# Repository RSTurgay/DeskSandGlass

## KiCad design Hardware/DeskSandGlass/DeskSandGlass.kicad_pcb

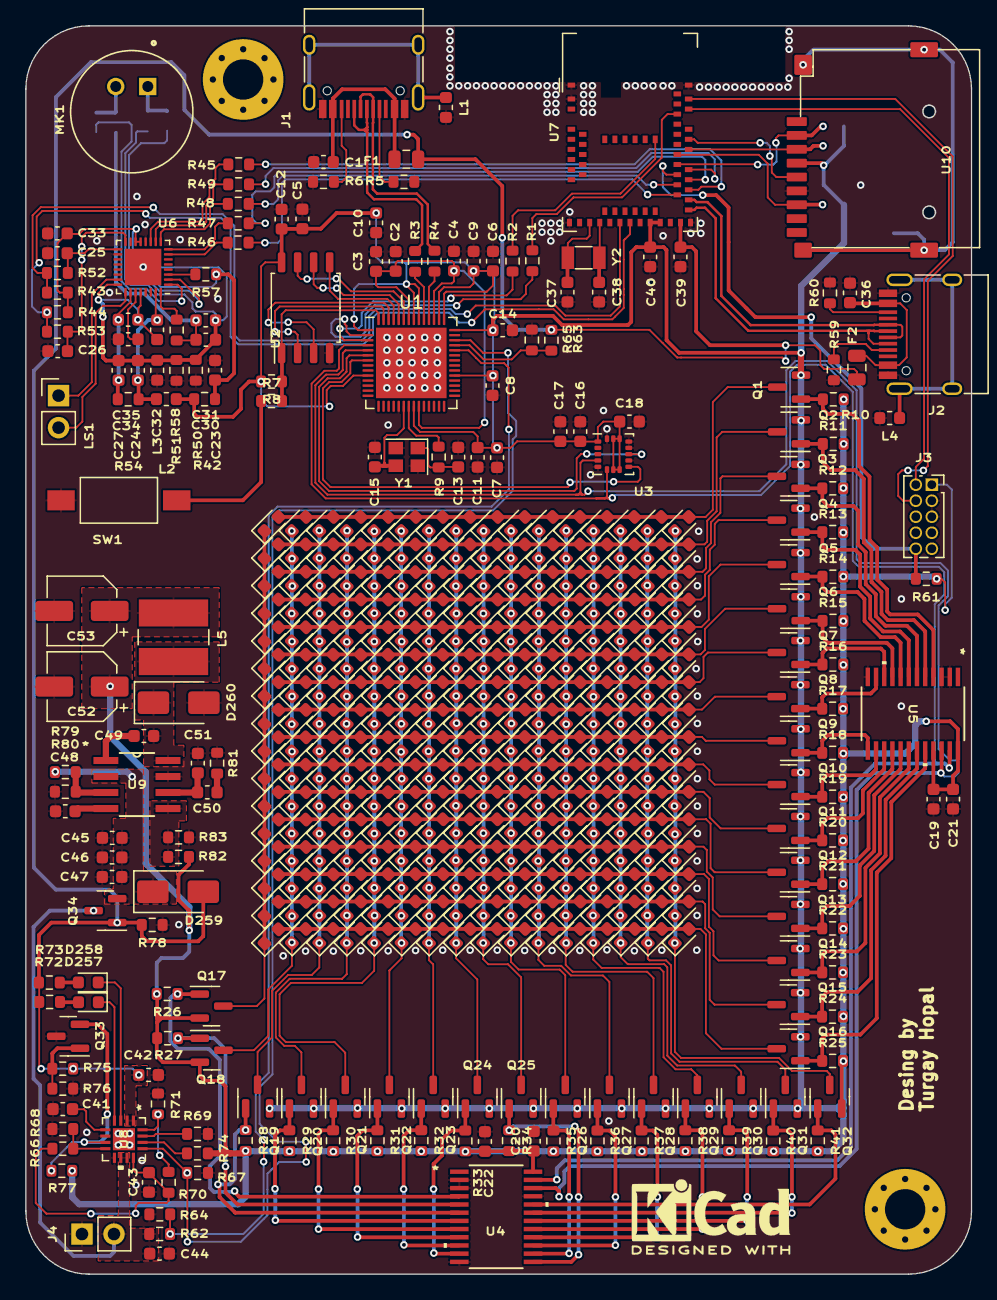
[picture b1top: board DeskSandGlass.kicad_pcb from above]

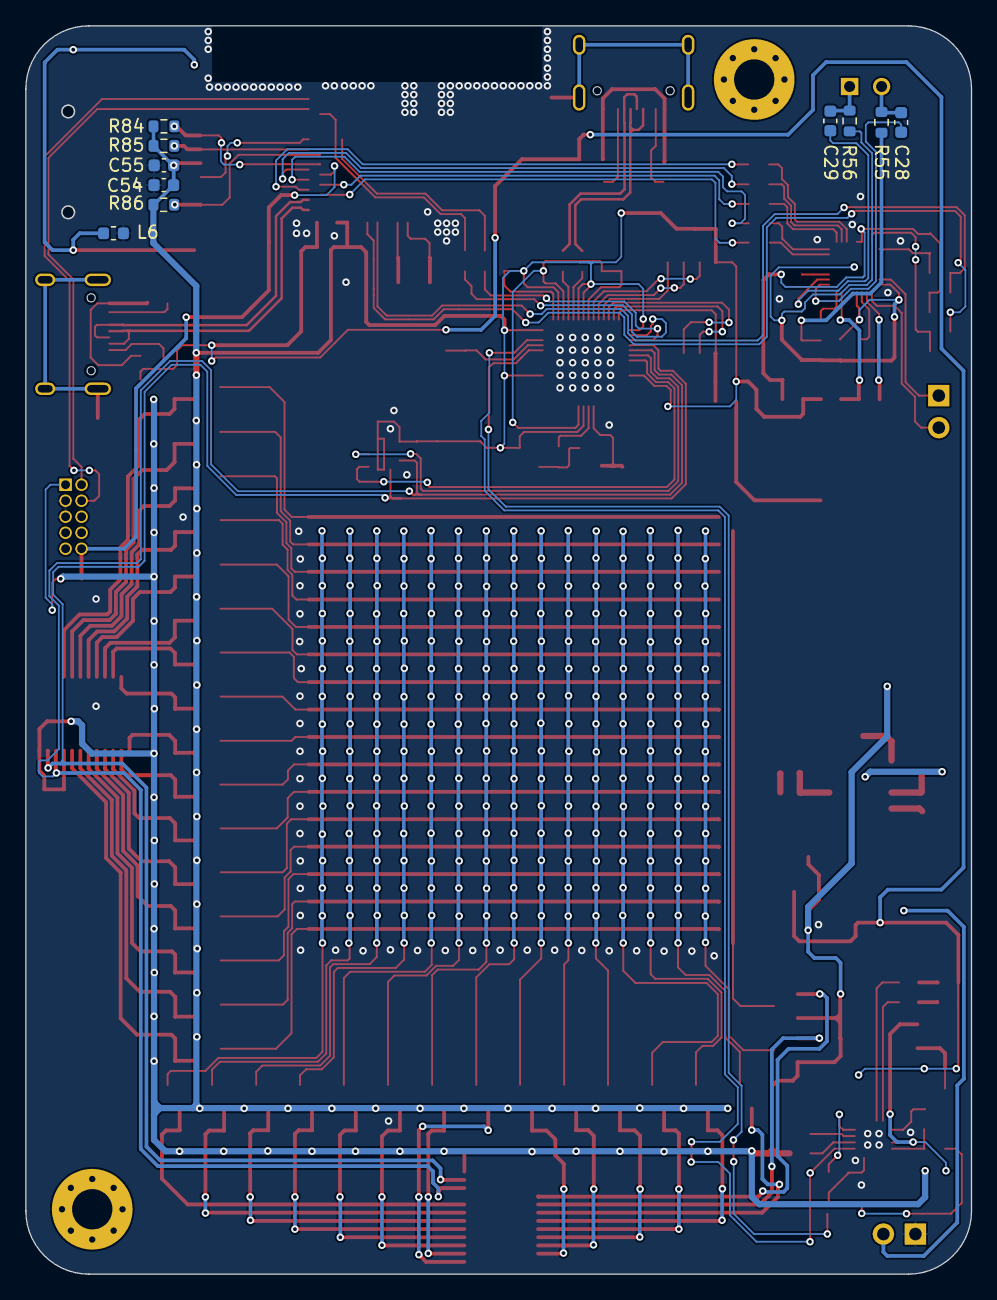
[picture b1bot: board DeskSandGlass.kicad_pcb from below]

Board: 2 copper layers, 75.0 x 99.0 mm, 462 parts (10 on the bottom side), 162 nets.

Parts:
C1, C4, C6, C21, C22, C28, C29, C36, C42: 1uF; C_0603_1608Metric
C2, C3, C5, C7, C8, C9, C10, C11, C12, C14, C16, C17, C19, C20, C31, C32, C33, C35, C54: 100nF; C_0603_1608Metric
C13, C15: 22pF; C_0603_1608Metric
C18, C23, C24, C25, C26, C27, C55: 10uF; C_0603_1608Metric
C30, C34, C39, C40, C44, C45, C46: 4.7uF; C_0603_1608Metric
C37, C38: 12pF; C_0603_1608Metric
C41, C47, C48: 10nF; C_0603_1608Metric
C43, C49, C50: 1nF; C_0603_1608Metric
C51: 47pF; C_0603_1608Metric
C52, C53: 47uF; CP_Elec_5x4.4
D1, D2, D3, D4, D5, D6, D7, D8, D9, D10, D11, D12, D13, D14, D15, D16, D17, D18, D19, D20, D21, D22, D23, D24, D25, D26, D27, D28, D29, D30, D31, D32, D33, D34, D35, D36, D37, D38, D39, D40, D41, D42, D43, D44, D45, D46, D47, D48, D49, D50, D51, D52, D53, D54, D55, D56, D57, D58, D59, D60, D61, D62, D63, D64, D65, D66, D67, D68, D69, D70, D71, D72, D73, D74, D75, D76, D77, D78, D79, D80, D81, D82, D83, D84, D85, D86, D87, D88, D89, D90, D91, D92, D93, D94, D95, D96, D97, D98, D99, D100, D101, D102, D103, D104, D105, D106, D107, D108, D109, D110, D111, D112, D113, D114, D115, D116, D117, D118, D119, D120, D121, D122, D123, D124, D125, D126, D127, D128, D129, D130, D131, D132, D133, D134, D135, D136, D137, D138, D139, D140, D141, D142, D143, D144, D145, D146, D147, D148, D149, D150, D151, D152, D153, D154, D155, D156, D157, D158, D159, D160, D161, D162, D163, D164, D165, D166, D167, D168, D169, D170, D171, D172, D173, D174, D175, D176, D177, D178, D179, D180, D181, D182, D183, D184, D185, D186, D187, D188, D189, D190, D191, D192, D193, D194, D195, D196, D197, D198, D199, D200, D201, D202, D203, D204, D205, D206, D207, D208, D209, D210, D211, D212, D213, D214, D215, D216, D217, D218, D219, D220, D221, D222, D223, D224, D225, D226, D227, D228, D229, D230, D231, D232, D233, D234, D235, D236, D237, D238, D239, D240, D241, D242, D243, D244, D245, D246, D247, D248, D249, D250, D251, D252, D253, D254, D255, D256, D257, D258: LED; LED_0603_1608Metric
D259: D; D_SMA
D260: B340; D_SMA
F1, F2: 6V/1.5A; Fuse_0805_2012Metric
J1, J2: USB_C_Receptacle_USB2.0; USB_C_Receptacle_HRO_TYPE-C-31-M-12
J3: NRF_Debug; PinSocket_2x05_P1.27mm_Vertical
J4: Conn_01x02_Male; PinHeader_1x02_P2.54mm_Vertical
L1, L4, L6: 220R; L_0603_1608Metric
L2, L3: FB; L_0603_1608Metric
L5: 6.8uH; L_TracoPower_TCK-047_5.2x5.8mm
LS1: Speaker; PinHeader_1x02_P2.54mm_Vertical
MK1: Microphone; MIC_CMA-4544PF-W
Q1, Q2, Q3, Q4, Q5, Q6, Q7, Q8, Q9, Q10, Q11, Q12, Q13, Q14, Q15, Q16, Q17, Q18, Q19, Q20, Q21, Q22, Q23, Q24, Q25, Q26, Q27, Q28, Q29, Q30, Q31, Q32: IRLML6402; SOT-23
Q33, Q34: IRLML5203; SOT-23
R1, R2, R42, R50, R51, R54: 0R; R_0603_1608Metric
R3, R4: 47R; R_0603_1608Metric
R5, R6, R59, R60: 5.1K; R_0603_1608Metric
R7, R9, R66, R72, R73, R75: 1K; R_0603_1608Metric
R8: DNF; R_0603_1608Metric
R10, R11, R12, R13, R14, R15, R16, R17, R18, R19, R20, R21, R22, R23, R24, R25, R26, R27, R28, R29, R30, R31, R32, R33, R34, R35, R36, R37, R38, R39, R40, R41, R61, R74, R76, R77, R84, R85, R86: 10K; R_0603_1608Metric
R43, R44, R52, R53: 33R; R_0603_1608Metric
R45, R46, R47, R48, R49: 220R; R_0603_1608Metric
R55, R56: 2.2K; R_0603_1608Metric
R57, R62, R63, R78, R80: 100K; R_0603_1608Metric
R58: 680R; R_0603_1608Metric
R64, R65: 200K; R_0603_1608Metric
R67: 3.3K; R_0603_1608Metric
R68: 470R; R_0603_1608Metric
R69: 24K; R_0603_1608Metric
R70: 39K; R_0603_1608Metric
R71: 62K; R_0603_1608Metric
R79: 150K; R_0603_1608Metric
R81: 29.4K; R_0603_1608Metric
R82: 10.2K; R_0603_1608Metric
R83: 3.24K; R_0603_1608Metric
SW1: BOOT; SW_SPST_FSMSM
U1: RP2040; QFN-56-1EP_7x7mm_P0.4mm_EP5.6x5.6mm
U2: W25Q128JVS; SOIC-8_5.23x5.23mm_P1.27mm
U3: LIS3DH; LGA-16_3x3mm_P0.5mm_LayoutBorder3x5y
U4, U5: PCA9535PWR; PW24_TEX
U6: NAU88C22; QFN-32-1EP_4x4mm_P0.4mm_EP2.9x2.9mm
U7: MDBT50Q-P1MV2; Raytac_MDBT50Q
U8: L6924D013TR
U9: TPS54331DR; D8
U10: L-KLS1-TF-003; L-KLS1-TF-003-H1.85-R
Y1: 12MHz; Crystal_SMD_2520-4Pin_2.5x2.0mm
Y2: 32.768kHz; Crystal_SMD_3215-2Pin_3.2x1.5mm

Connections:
+1V1: C2.1, C3.1, C4.1, U1.23 (DVDD), U1.45 (VREG_VOUT), U1.50 (DVDD)
+3V3: C5.1, C6.1, C7.1, C8.1, C9.1, C10.1, C11.1, C12.1, C14.1, C16.1, C17.1, C18.1, C19.1, C20.1, C21.1, C22.1, C40.2, C52.1, C53.1, C54.1, C55.1, J3.1, L2.1, L5.2, Q1.2 (S), Q2.2 (S), Q3.2 (S), Q4.2 (S), Q5.2 (S), Q6.2 (S), Q7.2 (S), Q8.2 (S), Q9.2 (S), Q10.2 (S), Q11.2 (S), Q12.2 (S), Q13.2 (S), Q14.2 (S), Q15.2 (S), Q16.2 (S), Q17.2 (S), Q18.2 (S), Q19.2 (S), Q20.2 (S), Q21.2 (S), Q22.2 (S), Q23.2 (S), Q24.2 (S), Q25.2 (S), Q26.2 (S), Q27.2 (S), Q28.2 (S), Q29.2 (S), Q30.2 (S), Q31.2 (S), Q32.2 (S), R8.2, R10.2, R11.2, R12.2, R13.2, R14.2, R15.2, R16.2, R17.2, R18.2, R19.2, R20.2, R21.2, R22.2, R23.2, R24.2, R25.2, R26.2, R27.2, R28.2, R29.2, R30.2, R31.2, R32.2, R33.2, R34.2, R35.2, R36.2, R37.2, R38.2, R39.2, R40.2, R41.2, R42.1, R61.2, R74.1, R77.1, R82.1, R84.1, R85.1, R86.2, U1.1 (IOVDD), U1.10 (IOVDD), U1.22 (IOVDD), U1.33 (IOVDD), U1.42 (IOVDD), U1.43 (ADC_AVDD), U1.44 (VREG_IN), U1.48 (USB_VDD), U1.49 (IOVDD), U2.8 (VCC), U3.1 (VDD_IO), U3.7 (SDO/SA0), U3.8 (CS), U3.14 (VDD), U3.15 (ADC2), U4.24 (VCC), U5.21 (A0), U5.24 (VCC), U7.28 (VDD), U7.30 (VDDH), U10.4 (VDD)
+BATT: C44.1, J4.2, Q34.3 (D), R62.1, U8.10 (VOSNS), U8.11 (VOUT)
/Audio/AUDIO_3V3: C24.2, C32.1, L2.2, R54.2, U6.31 (VDDA)
/Audio/AUDIO_D3V3: C23.2, C33.2, R42.2, R43.2, R44.2, R57.1, U6.13 (VDDC), U6.14 (VDDB)
/Audio/AUDIO_JKDET: R57.2, U6.3 (LLIN/GPIO2)
/Audio/I2S_BCLK: R47.2, U6.8 (BCLK)
/Audio/I2S_DI: R48.2, U6.9 (ADCOUT)
/Audio/I2S_DO: R49.2, U6.10 (DACIN)
/Audio/I2S_LRCK: R46.2, U6.7 (FS)
/Audio/I2S_MCLK: R45.2, U6.11 (MCLK)
/Audio/LMICN: C29.2, U6.2 (LMICN)
/Audio/LMICP: C28.2, U6.1 (LMICP)
/Audio/LSPKOUT: LS1.2, U6.25 (LSPKOUT)
/Audio/MIC_BIAS: C30.1, C31.1, R55.1, R58.2
/Audio/RSPKOUT: LS1.1, U6.23 (RSPKOUT)
/Audio/SCL: C26.1, R53.2, U6.16 (SCLK)
/Audio/SDA: C25.1, R52.2, U6.17 (SDIO)
/Audio/SPK_3V3: C27.2, C35.2, R54.1, U6.26 (VDDSPK)
/Audio/VREF: C34.2, U6.27 (VREF)
/L6924DV/IPRE: R70.2, R71.1, U8.16 (IPRE)
/L6924DV/SD: Q33.2 (S), R77.2, U8.7 (SD)
/L6924DV/TH: R66.1, R68.1, U8.8 (TH)
/L6924DV/VPRE: R74.2, U8.14 (VPRE)
/L6924DV/VREF: C43.1, R66.2, R70.1, U8.12 (VREF)
/LED's/C1: D1.1 (K), D2.1 (K), D3.1 (K), D4.1 (K), D5.1 (K), D6.1 (K), D7.1 (K), D8.1 (K), D9.1 (K), D10.1 (K), D11.1 (K), D12.1 (K), D13.1 (K), D14.1 (K), D15.1 (K), D16.1 (K), Q17.3 (D)
/LED's/C1_A: Q17.1 (G), R26.1, U4.4 (P00)
/LED's/C2: D17.1 (K), D18.1 (K), D19.1 (K), D20.1 (K), D21.1 (K), D22.1 (K), D23.1 (K), D24.1 (K), D25.1 (K), D26.1 (K), D27.1 (K), D28.1 (K), D29.1 (K), D30.1 (K), D31.1 (K), D32.1 (K), Q18.3 (D)
/LED's/C2_A: Q18.1 (G), R27.1, U4.5 (P01)
/LED's/C3: D33.1 (K), D34.1 (K), D35.1 (K), D36.1 (K), D37.1 (K), D38.1 (K), D39.1 (K), D40.1 (K), D41.1 (K), D42.1 (K), D43.1 (K), D44.1 (K), D45.1 (K), D46.1 (K), D47.1 (K), D48.1 (K), Q19.3 (D)
/LED's/C3_A: Q19.1 (G), R28.1, U4.6 (P02)
/LED's/C4: D49.1 (K), D50.1 (K), D51.1 (K), D52.1 (K), D53.1 (K), D54.1 (K), D55.1 (K), D56.1 (K), D57.1 (K), D58.1 (K), D59.1 (K), D60.1 (K), D61.1 (K), D62.1 (K), D63.1 (K), D64.1 (K), Q20.3 (D)
/LED's/C4_A: Q20.1 (G), R29.1, U4.7 (P03)
/LED's/C5: D65.1 (K), D66.1 (K), D67.1 (K), D68.1 (K), D69.1 (K), D70.1 (K), D71.1 (K), D72.1 (K), D73.1 (K), D74.1 (K), D75.1 (K), D76.1 (K), D77.1 (K), D78.1 (K), D79.1 (K), D80.1 (K), Q21.3 (D)
/LED's/C5_A: Q21.1 (G), R30.1, U4.8 (P04)
/LED's/C6: D81.1 (K), D82.1 (K), D83.1 (K), D84.1 (K), D85.1 (K), D86.1 (K), D87.1 (K), D88.1 (K), D89.1 (K), D90.1 (K), D91.1 (K), D92.1 (K), D93.1 (K), D94.1 (K), D95.1 (K), D96.1 (K), Q22.3 (D)
/LED's/C6_A: Q22.1 (G), R31.1, U4.9 (P05)
/LED's/C7: D97.1 (K), D98.1 (K), D99.1 (K), D100.1 (K), D101.1 (K), D102.1 (K), D103.1 (K), D104.1 (K), D105.1 (K), D106.1 (K), D107.1 (K), D108.1 (K), D109.1 (K), D110.1 (K), D111.1 (K), D112.1 (K), Q23.3 (D)
/LED's/C7_A: Q23.1 (G), R32.1, U4.10 (P06)
/LED's/C8: D113.1 (K), D114.1 (K), D115.1 (K), D116.1 (K), D117.1 (K), D118.1 (K), D119.1 (K), D120.1 (K), D121.1 (K), D122.1 (K), D123.1 (K), D124.1 (K), D125.1 (K), D126.1 (K), D127.1 (K), D128.1 (K), Q24.3 (D)
/LED's/C8_A: Q24.1 (G), R33.1, U4.11 (P07)
/LED's/C9: D129.1 (K), D130.1 (K), D131.1 (K), D132.1 (K), D133.1 (K), D134.1 (K), D135.1 (K), D136.1 (K), D137.1 (K), D138.1 (K), D139.1 (K), D140.1 (K), D141.1 (K), D142.1 (K), D143.1 (K), D144.1 (K), Q25.3 (D)
/LED's/C9_A: Q25.1 (G), R34.1, U4.13 (P10)
/LED's/C10: D145.1 (K), D146.1 (K), D147.1 (K), D148.1 (K), D149.1 (K), D150.1 (K), D151.1 (K), D152.1 (K), D153.1 (K), D154.1 (K), D155.1 (K), D156.1 (K), D157.1 (K), D158.1 (K), D159.1 (K), D160.1 (K), Q26.3 (D)
/LED's/C10_A: Q26.1 (G), R35.1, U4.14 (P11)
/LED's/C11: D161.1 (K), D162.1 (K), D163.1 (K), D164.1 (K), D165.1 (K), D166.1 (K), D167.1 (K), D168.1 (K), D169.1 (K), D170.1 (K), D171.1 (K), D172.1 (K), D173.1 (K), D174.1 (K), D175.1 (K), D176.1 (K), Q27.3 (D)
/LED's/C11_A: Q27.1 (G), R36.1, U4.15 (P12)
/LED's/C12: D177.1 (K), D178.1 (K), D179.1 (K), D180.1 (K), D181.1 (K), D182.1 (K), D183.1 (K), D184.1 (K), D185.1 (K), D186.1 (K), D187.1 (K), D188.1 (K), D189.1 (K), D190.1 (K), D191.1 (K), D192.1 (K), Q28.3 (D)
/LED's/C12_A: Q28.1 (G), R37.1, U4.16 (P13)
/LED's/C13: D193.1 (K), D194.1 (K), D195.1 (K), D196.1 (K), D197.1 (K), D198.1 (K), D199.1 (K), D200.1 (K), D201.1 (K), D202.1 (K), D203.1 (K), D204.1 (K), D205.1 (K), D206.1 (K), D207.1 (K), D208.1 (K), Q29.3 (D)
/LED's/C13_A: Q29.1 (G), R38.1, U4.17 (P14)
/LED's/C14: D209.1 (K), D210.1 (K), D211.1 (K), D212.1 (K), D213.1 (K), D214.1 (K), D215.1 (K), D216.1 (K), D217.1 (K), D218.1 (K), D219.1 (K), D220.1 (K), D221.1 (K), D222.1 (K), D223.1 (K), D224.1 (K), Q30.3 (D)
/LED's/C14_A: Q30.1 (G), R39.1, U4.18 (P15)
/LED's/C15: D225.1 (K), D226.1 (K), D227.1 (K), D228.1 (K), D229.1 (K), D230.1 (K), D231.1 (K), D232.1 (K), D233.1 (K), D234.1 (K), D235.1 (K), D236.1 (K), D237.1 (K), D238.1 (K), D239.1 (K), D240.1 (K), Q31.3 (D)
/LED's/C15_A: Q31.1 (G), R40.1, U4.19 (P16)
/LED's/C16: D241.1 (K), D242.1 (K), D243.1 (K), D244.1 (K), D245.1 (K), D246.1 (K), D247.1 (K), D248.1 (K), D249.1 (K), D250.1 (K), D251.1 (K), D252.1 (K), D253.1 (K), D254.1 (K), D255.1 (K), D256.1 (K), Q32.3 (D)
/LED's/C16_A: Q32.1 (G), R41.1, U4.20 (P17)
/LED's/R1: D1.2 (A), D17.2 (A), D33.2 (A), D49.2 (A), D65.2 (A), D81.2 (A), D97.2 (A), D113.2 (A), D129.2 (A), D145.2 (A), D161.2 (A), D177.2 (A), D193.2 (A), D209.2 (A), D225.2 (A), D241.2 (A), Q1.3 (D)
/LED's/R1_A: Q1.1 (G), R10.1, U5.4 (P00)
/LED's/R2: D2.2 (A), D18.2 (A), D34.2 (A), D50.2 (A), D66.2 (A), D82.2 (A), D98.2 (A), D114.2 (A), D130.2 (A), D146.2 (A), D162.2 (A), D178.2 (A), D194.2 (A), D210.2 (A), D226.2 (A), D242.2 (A), Q2.3 (D)
/LED's/R2_A: Q2.1 (G), R11.1, U5.5 (P01)
/LED's/R3: D3.2 (A), D19.2 (A), D35.2 (A), D51.2 (A), D67.2 (A), D83.2 (A), D99.2 (A), D115.2 (A), D131.2 (A), D147.2 (A), D163.2 (A), D179.2 (A), D195.2 (A), D211.2 (A), D227.2 (A), D243.2 (A), Q3.3 (D)
/LED's/R3_A: Q3.1 (G), R12.1, U5.6 (P02)
/LED's/R4: D4.2 (A), D20.2 (A), D36.2 (A), D52.2 (A), D68.2 (A), D84.2 (A), D100.2 (A), D116.2 (A), D132.2 (A), D148.2 (A), D164.2 (A), D180.2 (A), D196.2 (A), D212.2 (A), D228.2 (A), D244.2 (A), Q4.3 (D)
/LED's/R4_A: Q4.1 (G), R13.1, U5.7 (P03)
/LED's/R5: D5.2 (A), D21.2 (A), D37.2 (A), D53.2 (A), D69.2 (A), D85.2 (A), D101.2 (A), D117.2 (A), D133.2 (A), D149.2 (A), D165.2 (A), D181.2 (A), D197.2 (A), D213.2 (A), D229.2 (A), D245.2 (A), Q5.3 (D)
/LED's/R5_A: Q5.1 (G), R14.1, U5.8 (P04)
/LED's/R6: D6.2 (A), D22.2 (A), D38.2 (A), D54.2 (A), D70.2 (A), D86.2 (A), D102.2 (A), D118.2 (A), D134.2 (A), D150.2 (A), D166.2 (A), D182.2 (A), D198.2 (A), D214.2 (A), D230.2 (A), D246.2 (A), Q6.3 (D)
/LED's/R6_A: Q6.1 (G), R15.1, U5.9 (P05)
/LED's/R7: D7.2 (A), D23.2 (A), D39.2 (A), D55.2 (A), D71.2 (A), D87.2 (A), D103.2 (A), D119.2 (A), D135.2 (A), D151.2 (A), D167.2 (A), D183.2 (A), D199.2 (A), D215.2 (A), D231.2 (A), D247.2 (A), Q7.3 (D)
/LED's/R7_A: Q7.1 (G), R16.1, U5.10 (P06)
/LED's/R8: D8.2 (A), D24.2 (A), D40.2 (A), D56.2 (A), D72.2 (A), D88.2 (A), D104.2 (A), D120.2 (A), D136.2 (A), D152.2 (A), D168.2 (A), D184.2 (A), D200.2 (A), D216.2 (A), D232.2 (A), D248.2 (A), Q8.3 (D)
/LED's/R8_A: Q8.1 (G), R17.1, U5.11 (P07)
/LED's/R9: D9.2 (A), D25.2 (A), D41.2 (A), D57.2 (A), D73.2 (A), D89.2 (A), D105.2 (A), D121.2 (A), D137.2 (A), D153.2 (A), D169.2 (A), D185.2 (A), D201.2 (A), D217.2 (A), D233.2 (A), D249.2 (A), Q9.3 (D)
/LED's/R9_A: Q9.1 (G), R18.1, U5.13 (P10)
/LED's/R10: D10.2 (A), D26.2 (A), D42.2 (A), D58.2 (A), D74.2 (A), D90.2 (A), D106.2 (A), D122.2 (A), D138.2 (A), D154.2 (A), D170.2 (A), D186.2 (A), D202.2 (A), D218.2 (A), D234.2 (A), D250.2 (A), Q10.3 (D)
/LED's/R10_A: Q10.1 (G), R19.1, U5.14 (P11)
/LED's/R11: D11.2 (A), D27.2 (A), D43.2 (A), D59.2 (A), D75.2 (A), D91.2 (A), D107.2 (A), D123.2 (A), D139.2 (A), D155.2 (A), D171.2 (A), D187.2 (A), D203.2 (A), D219.2 (A), D235.2 (A), D251.2 (A), Q11.3 (D)
/LED's/R11_A: Q11.1 (G), R20.1, U5.15 (P12)
/LED's/R12: D12.2 (A), D28.2 (A), D44.2 (A), D60.2 (A), D76.2 (A), D92.2 (A), D108.2 (A), D124.2 (A), D140.2 (A), D156.2 (A), D172.2 (A), D188.2 (A), D204.2 (A), D220.2 (A), D236.2 (A), D252.2 (A), Q12.3 (D)
/LED's/R12_A: Q12.1 (G), R21.1, U5.16 (P13)
/LED's/R13: D13.2 (A), D29.2 (A), D45.2 (A), D61.2 (A), D77.2 (A), D93.2 (A), D109.2 (A), D125.2 (A), D141.2 (A), D157.2 (A), D173.2 (A), D189.2 (A), D205.2 (A), D221.2 (A), D237.2 (A), D253.2 (A), Q13.3 (D)
/LED's/R13_A: Q13.1 (G), R22.1, U5.17 (P14)
/LED's/R14: D14.2 (A), D30.2 (A), D46.2 (A), D62.2 (A), D78.2 (A), D94.2 (A), D110.2 (A), D126.2 (A), D142.2 (A), D158.2 (A), D174.2 (A), D190.2 (A), D206.2 (A), D222.2 (A), D238.2 (A), D254.2 (A), Q14.3 (D)
/LED's/R14_A: Q14.1 (G), R23.1, U5.18 (P15)
/LED's/R15: D15.2 (A), D31.2 (A), D47.2 (A), D63.2 (A), D79.2 (A), D95.2 (A), D111.2 (A), D127.2 (A), D143.2 (A), D159.2 (A), D175.2 (A), D191.2 (A), D207.2 (A), D223.2 (A), D239.2 (A), D255.2 (A), Q15.3 (D)
/LED's/R15_A: Q15.1 (G), R24.1, U5.19 (P16)
/LED's/R16: D16.2 (A), D32.2 (A), D48.2 (A), D64.2 (A), D80.2 (A), D96.2 (A), D112.2 (A), D128.2 (A), D144.2 (A), D160.2 (A), D176.2 (A), D192.2 (A), D208.2 (A), D224.2 (A), D240.2 (A), D256.2 (A), Q16.3 (D)
/LED's/R16_A: Q16.1 (G), R25.1, U5.20 (P17)
/NRF5280 Module/NRESET: J3.10, R61.1, U7.40 (~RESET/P0.18)
/NRF5280 Module/SWDCLK: J3.4, U7.53 (SWDCLK)
/NRF5280 Module/SWDIO: J3.2, U7.51 (SWDIO)
/NRF5280 Module/USB_D+: J2.A6 (D+), J2.B6 (D+), U7.35 (D+)
/NRF5280 Module/USB_D-: J2.A7 (D-), J2.B7 (D-), U7.34 (D-)
/NRF5280 Module/XL1: C37.1, U7.17 (XL1/P0.00), Y2.1
/NRF5280 Module/XL2: C38.1, U7.18 (XL2/P0.01), Y2.2
/RP2040/QSPI_SCLK: U1.52 (QSPI_SCLK), U2.6 (CLK)
/RP2040/QSPI_SD0: U1.53 (QSPI_SD0), U2.5 (DI(IO0))
/RP2040/QSPI_SD1: U1.55 (QSPI_SD1), U2.2 (DO(IO1))
/RP2040/QSPI_SD2: U1.54 (QSPI_SD2), U2.3 (IO2)
/RP2040/QSPI_SD3: U1.51 (QSPI_SD3), U2.7 (IO3)
/RP2040/QSPI_SS: R7.2, R8.1, U1.56 (QSPI_SS), U2.1 (~CS)
/RP2040/USB_D+: J1.A6 (D+), J1.B6 (D+), R3.1
/RP2040/USB_D-: J1.A7 (D-), J1.B7 (D-), R4.1
/RP2040/USB_DM: R4.2, U1.46 (USB_DM)
/RP2040/USB_DP: R3.2, U1.47 (USB_DP)
/RP2040/XIN: C15.1, U1.20 (XIN), Y1.3
/RP2040/XOUT: R9.2, U1.21 (XOUT)
/TPS54331/BOOT: C49.1, D260.1 (K), L5.1, U9.8 (PH)
/TPS54331/VIN: C45.1, C46.1, C47.1, D259.1 (K), Q34.2 (S), R79.1, U9.2 (VIN)
/TPS54331/VSENSE: R82.2, R83.1, U9.5 (VSENSE)
ADC0: R62.2, R64.2, U1.38 (GPIO26_ADC0)
ADC1: R63.1, R65.1, U1.39 (GPIO27_ADC1)
ADC2: R67.1, U1.40 (GPIO28_ADC2), U8.13 (IEND)
GND: C1.1, C2.2, C3.2, C4.2, C5.2, C6.2, C7.2, C8.2, C9.2, C10.2, C11.2, C12.2, C13.2, C14.2, C15.2, C16.2, C17.2, C18.2, C19.2, C20.2, C21.2, C22.2, C23.1, C25.2, C26.2, C33.1, C34.1, C36.1, C37.2, C38.2, C39.1, C40.1, C41.2, C42.2, C43.2, C44.2, C45.2, C46.2, C47.2, C48.2, C51.2, C52.2, C53.2, C54.2, C55.2, D260.2 (A), J1.A1 (GND), J1.A12 (GND), J1.B1 (GND), J1.B12 (GND), J2.A1 (GND), J2.A12 (GND), J2.B1 (GND), J2.B12 (GND), J3.3, J3.5, J4.1, L1.2, L3.1, L4.2, L6.2, Q33.3 (D), R5.2, R6.2, R50.2, R51.2, R59.2, R60.2, R64.1, R65.2, R67.2, R68.2, R69.2, R71.2, R76.1, R78.1, R80.2, R81.2, R83.2, SW1.1, U1.19 (TESTEN), U1.57 (GND), U2.4 (GND), U3.5 (GND), U3.10 (GND), U3.12 (GND), U3.13 (ADC3), U3.16 (ADC1), U4.2 (A1), U4.3 (A2), U4.12 (GND), U4.21 (A0), U5.2 (A1), U5.3 (A2), U5.12 (GND), U6.12 (VSSD), U6.18 (MODE), U7.1 (GND), U7.2 (GND), U7.15 (GND), U7.33 (GND), U7.55 (GND), U8.6 (GND), U8.9 (VOPRG), U8.17, U9.7 (GND), U10.6 (VSS), Y1.2, Y1.4
GPIO0: R1.1, U1.2 (GPIO0)
GPIO1: R2.1, U1.3 (GPIO1)
GPIO2: U1.4 (GPIO2), U3.6 (SDA/SDI/SDO), U4.23 (SDA), U5.23 (SDA)
GPIO3: U1.5 (GPIO3), U3.4 (SCL/SPC), U4.22 (SCL), U5.22 (SCL)
GPIO4: U1.6 (GPIO4), U3.11 (INT1)
GPIO5: U1.7 (GPIO5), U3.9 (INT2)
unnamed: C1.2, F1.1, J1.A4 (VBUS), J1.A9 (VBUS), J1.B4 (VBUS), J1.B9 (VBUS)
unnamed: C13.1, R9.1, Y1.1
unnamed: C36.2, F2.1, J2.A4 (VBUS), J2.A9 (VBUS), J2.B4 (VBUS), J2.B9 (VBUS)
unnamed: C50.2, R81.1
unnamed: D257.2 (A), R72.1
unnamed: D257.1 (K), U8.4 (ST1)
unnamed: D258.2 (A), R73.1
unnamed: D258.1 (K), U8.3 (ST2)
unnamed: J1.A5 (CC1), R5.1
unnamed: J1.B5 (CC2), R6.1
unnamed: J1.S1 (SHIELD), L1.1
unnamed: J2.A5 (CC1), R59.1
unnamed: J2.B5 (CC2), R60.1
unnamed: J2.S1 (SHIELD), L4.1
unnamed: L6.1, U10.10 (SHIELD), U10.11 (SHIELD), U10.12 (SHIELD), U10.13 (SHIELD)
unnamed: C28.1, MK1.2 (+), R55.2
unnamed: C29.1, MK1.1 (-), R56.1
unnamed: Q33.1 (G), R75.1, R76.2
unnamed: R7.1, SW1.2
unnamed: R58.1, U6.32 (MICBIAS)
unnamed: R69.1, U8.15 (IPRG)
unnamed: C41.1, U8.5 (TPRG)
unnamed: C49.2, U9.1 (BOOT)
unnamed: C50.1, C51.1, U9.6 (COMP)
unnamed: R79.2, R80.1, U9.3 (EN)
unnamed: C48.1, U9.4 (SS)
P0.06: R43.1, R52.1, U7.22 (P0.06)
P0.08: R44.1, R53.1, U7.24 (P0.08)
P0.13: R45.1, U7.37 (P0.13)
P0.14: R46.1, U7.36 (P0.14)
P0.15: R47.1, U7.39 (P0.15)
P0.16: R48.1, U7.38 (P0.16)
P0.17: R49.1, U7.41 (P0.17)
P0.19: R84.2, U7.42 (P0.19), U10.2 (CD/DAT3)
P0.20: R85.2, U7.44 (P0.20), U10.3 (CMD)
P0.21: R86.1, U7.43 (P0.21), U10.7 (DAT0)
P0.22: U7.46 (P0.22), U10.5 (CLK)
P1.01: R2.2, U7.61 (P1.01)
P1.02: R1.2, U7.50 (P1.02)
VBUS: C39.2, C42.1, D259.2 (A), F1.2, F2.2, Q34.1 (G), R63.2, R72.2, R73.2, R75.2, R78.2, U7.32 (VBUS), U8.1 (VIN), U8.2 (VINSNS)
VSSA: C24.1, C27.1, C30.2, C31.2, C32.2, C35.1, L3.2, R50.1, R51.1, R56.2, U6.24 (VSSSPK), U6.28 (VSSA), U6.33 (EPAD)

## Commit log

2023-08-05 First Init

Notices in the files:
parts and their libraries:
Copyright 2021 Accelerated Designs. All rights reserved.
